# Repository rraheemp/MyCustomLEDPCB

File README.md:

# LED Driver Prototype System
## Overview
This project consist of a FPGA based board (Artix 7 Basys3) and a custom STM32-driven board with 2 IS31FL3743B SPI LED Matrix drivers and breakouts for adding other peripheral. Each LED can have its brightness and state controlled through the API functions. The FPGA will provide the master signals through a SPI header breakout on the custom board.

## Ideas for the future include:

- Desktop Dashboard GUI 
- IoT Dashboard

This is a personal project and as such, may not work 100% but is a continued learning experience for me. Feel free to use the code in your project if it seems useful or insightful.

### Renders:
#### Front: 

*This board has not be verified as of 3/21/2022 and should not be ordered until I verify it.*

## IS31Fl3743B

> The IS31FL3743B is a general purpose 18×n (n=1~11) 
LED Matrix programmed via 12MHz SPI interface. 
Each LED can be dimmed individually with 8-bit PWM 
data and 8-bit DC scaling data which allowing 256 
steps of linear PWM dimming and 256 steps of DC 
current adjustable level. -*Lumissil* 

### Library

The folder *IS31FL3743B Driver* contains the library of functions for illuminating the board. These functions are derived from the data sheet following the following SPI Data Scheme.

### Registers
There following tables define the registers and their appropriate values.
#### Pwm:

#### Scaling:

#### Configurations:

## *Coming Soon*

# STM32G031F6P6
> The STM32G031x4/x6/x8 mainstream microcontrollers are based on high-performance 
Arm® Cortex®-M0+ 32-bit RISC core operating at up to 64 MHz frequency. Offering a high 
level of integration, they are suitable for a wide range of applications in consumer, industrial 
and appliance domains and ready for the Internet of Things (IoT) solutions.

*ST*

## *Coming Soon*

# Basys 3 Artix-7 

> Complete and ready-to use digital circuit development platform, it includes enough switches, LEDs, and other I/O devices to allow a large number of designs to be completed without the need for any additional hardware. There are also enough uncommitted FPGA I/O pins to allow designs to be expanded using Digilent Pmods or other custom boards and circuits.

*Diligent*

## *Coming Soon*

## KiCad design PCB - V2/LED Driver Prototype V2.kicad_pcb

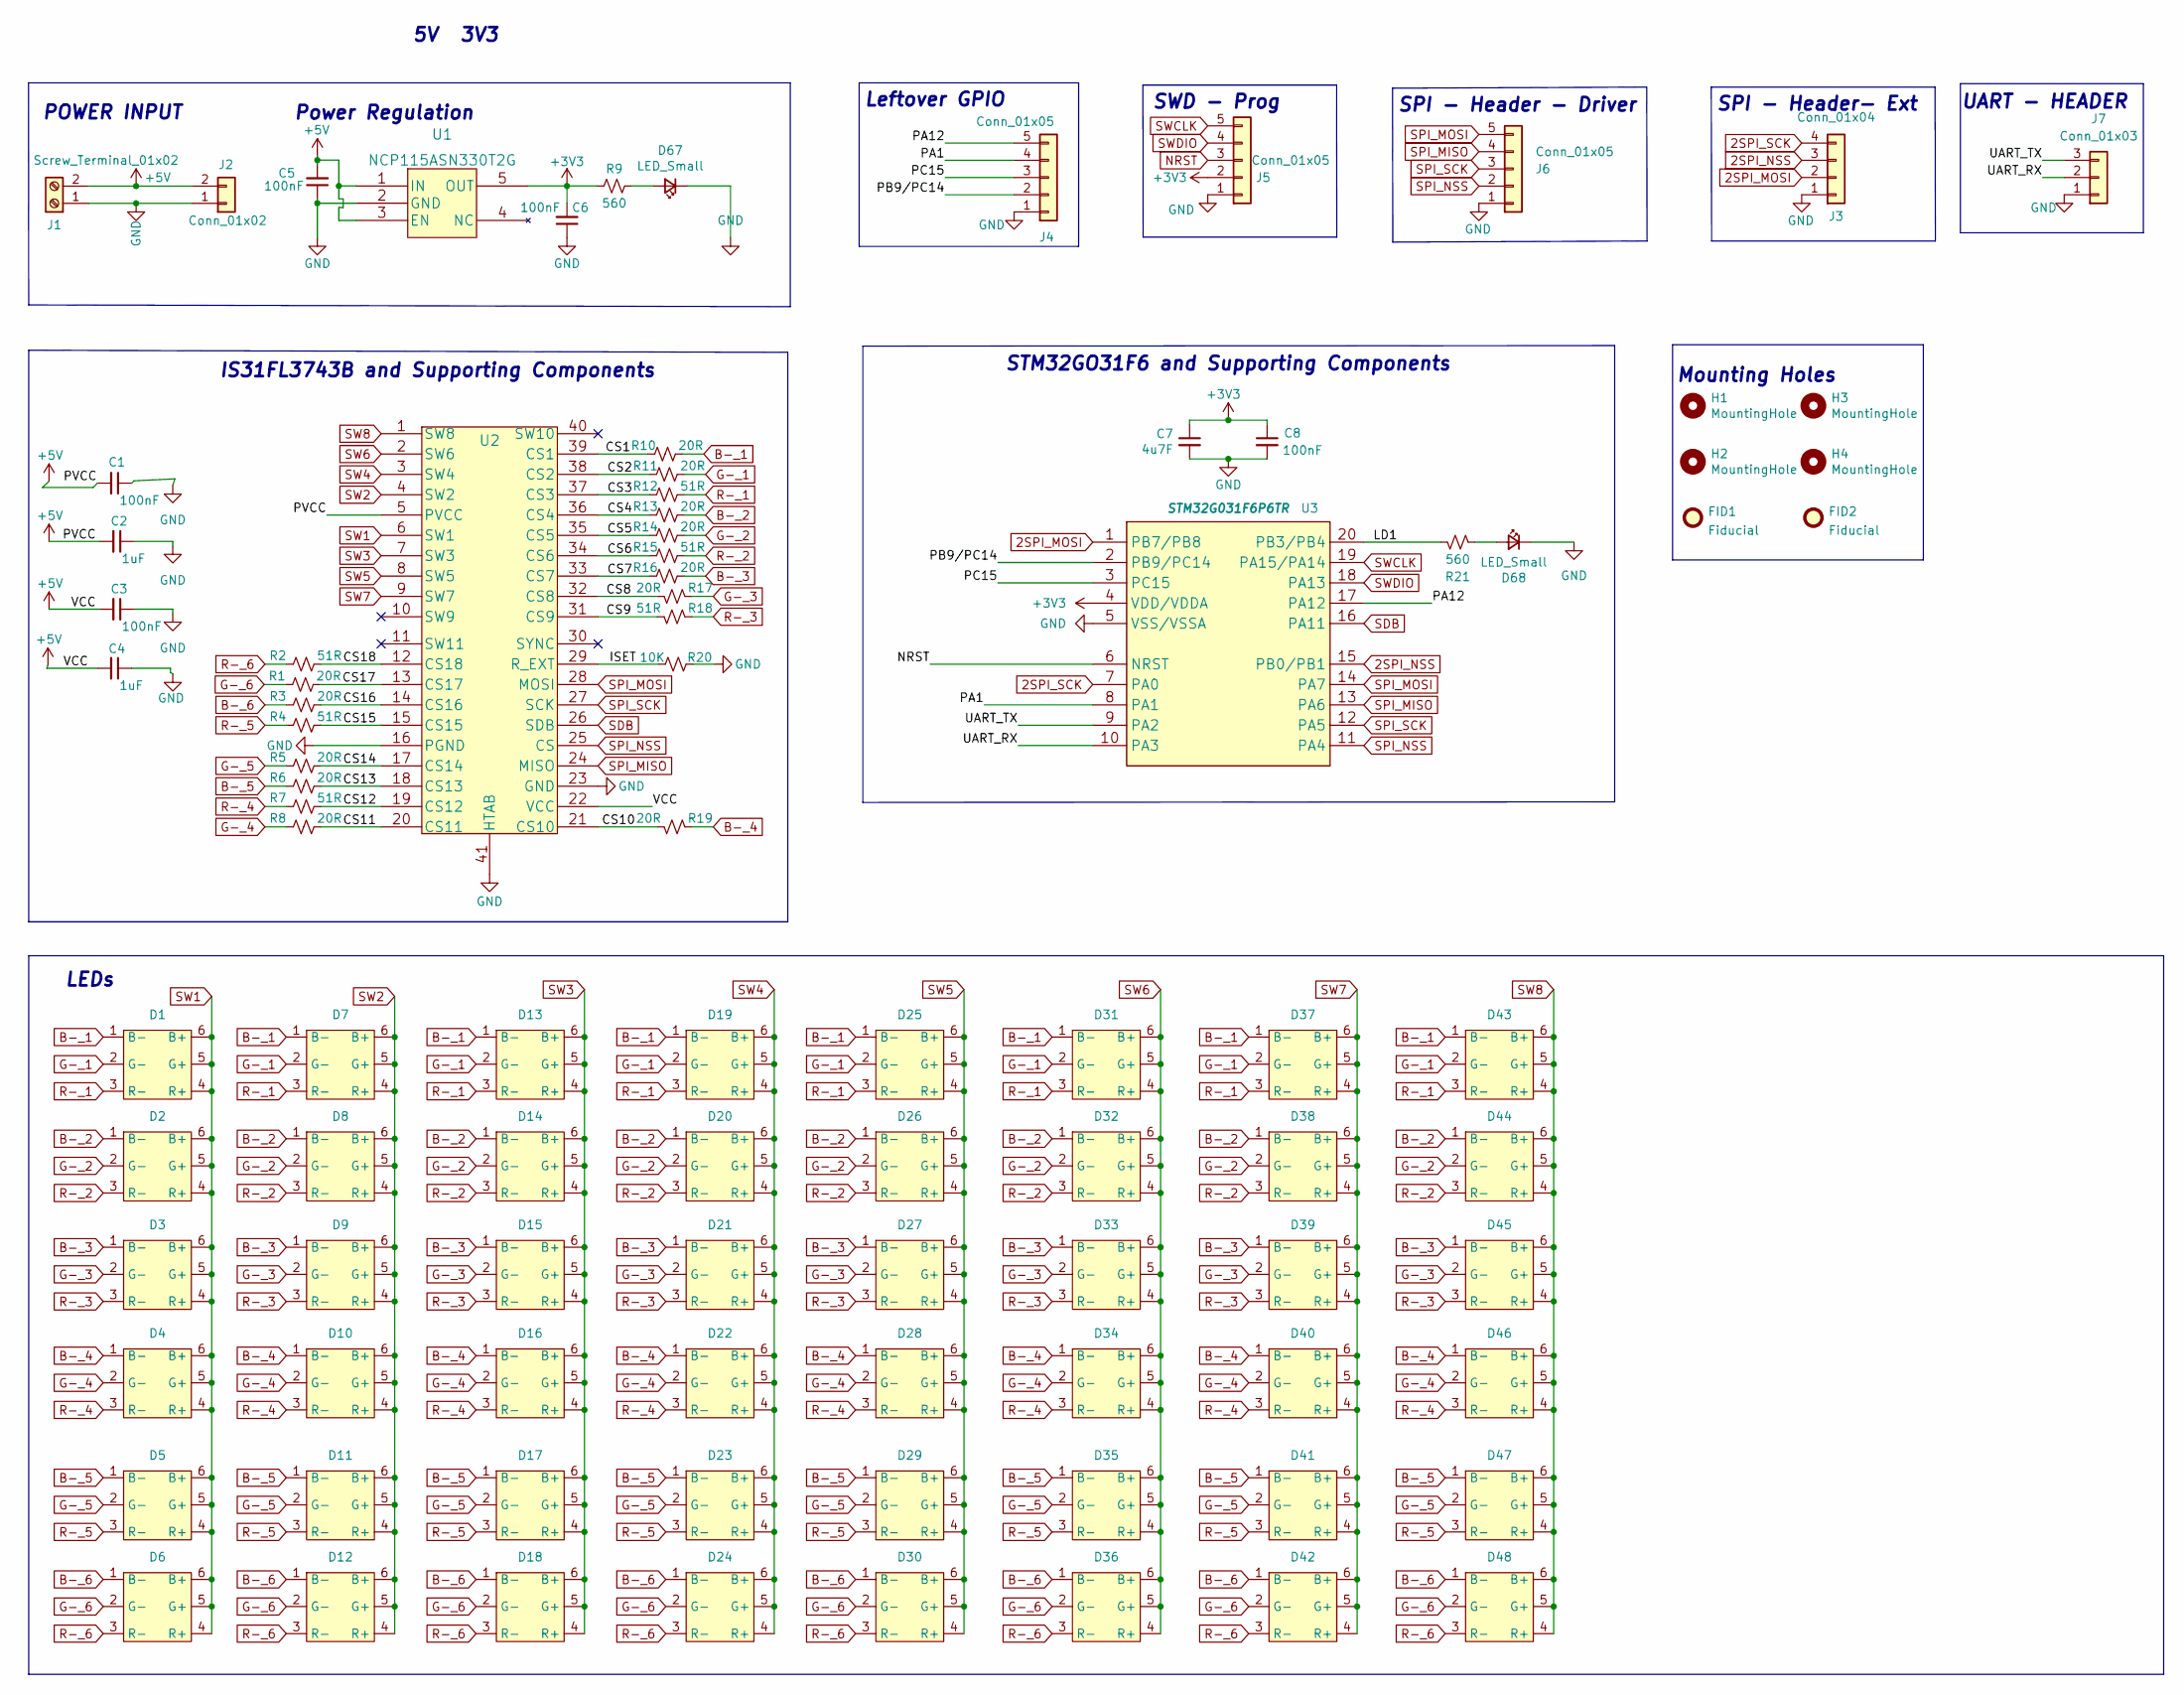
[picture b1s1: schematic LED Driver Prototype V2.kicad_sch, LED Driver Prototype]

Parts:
C1, C3, C5, C6, C8: 100nF; C_0603_1608Metric_Pad1.08x0.95mm_HandSolder
C2, C4: 1uF; C_0603_1608Metric_Pad1.08x0.95mm_HandSolder
C7: 4u7F; C_0603_1608Metric_Pad1.08x0.95mm_HandSolder
D1, D2, D3, D4, D5, D6, D7, D8, D9, D10, D11, D12, D13, D14, D15, D16, D17, D18, D19, D20, D21, D22, D23, D24, D25, D26, D27, D28, D29, D30, D31, D32, D33, D34, D35, D36, D37, D38, D39, D40, D41, D42, D43, D44, D45, D46, D47, D48: MHP3535RGBDT-S_-_PLCC_-_6; MHP3535RGBDT-S
D67: LED_Small; LTST-C191KRKT
D68: LED_Small; LTST-C191KGKT
FID1, FID2: Fiducial; Fiducial_0.5mm_Mask1.5mm
H1, H2, H3, H4: MountingHole; MountingHole_2.2mm_M2_ISO7380_Pad
J1: Screw_Terminal_01x02; TerminalBlock_TE_282834-2_1x02_P2.54mm_Horizontal
J2: Conn_01x02; PinHeader_1x02_P2.54mm_Vertical
J3: Conn_01x04; PinHeader_1x04_P2.54mm_Vertical
J4, J5, J6: Conn_01x05; PinHeader_1x05_P2.54mm_Vertical
J7: Conn_01x03; PinHeader_1x03_P2.54mm_Vertical
R1, R3, R5, R6, R8, R10, R11, R13, R14, R16, R17, R19: 20R; R_0603_1608Metric_Pad0.98x0.95mm_HandSolder
R2, R4, R7, R12, R15, R18: 51R; R_0603_1608Metric_Pad0.98x0.95mm_HandSolder
R9, R21: 560; R_0603_1608Metric_Pad0.98x0.95mm_HandSolder
R20: 10K; R_0603_1608Metric_Pad0.98x0.95mm_HandSolder
U1: NCP115ASN330T2G
U2: IS31FL3743B-QULS4-TR
U3: STM32G031F6P6TR; STM32G031F6P6

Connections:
2SPI_MOSI: J3.2, U3.1 (PB7/PB8)
2SPI_NSS: J3.3, U3.15 (PB0/PB1)
2SPI_SCK: J3.4, U3.7 (PA0)
+3V3: C6.2, C7.1, C8.1, J5.2, R9.2, U1.5 (OUT), U3.4 (VDD/VDDA)
+5V: C1.2, C2.2, C3.2, C4.2, C5.2, J1.2, J2.2, U1.1 (IN), U1.3 (EN), U2.5 (PVCC), U2.22 (VCC)
/CS1: R10.2, U2.39 (CS1)
/CS2: R11.2, U2.38 (CS2)
/CS3: R12.2, U2.37 (CS3)
/CS4: R13.2, U2.36 (CS4)
/CS5: R14.2, U2.35 (CS5)
/CS6: R15.2, U2.34 (CS6)
/CS7: R16.2, U2.33 (CS7)
/CS8: R17.1, U2.32 (CS8)
/CS9: R18.1, U2.31 (CS9)
/CS10: R19.1, U2.21 (CS10)
/CS11: R8.1, U2.20 (CS11)
/CS12: R7.1, U2.19 (CS12)
/CS13: R6.1, U2.18 (CS13)
/CS14: R5.1, U2.17 (CS14)
/CS15: R4.1, U2.15 (CS15)
/CS16: R3.1, U2.14 (CS16)
/CS17: R1.1, U2.13 (CS17)
/CS18: R2.1, U2.12 (CS18)
/ISET: R20.1, U2.29 (R_EXT)
/LD1: R21.2, U3.20 (PB3/PB4)
/PA1: J4.4, U3.8 (PA1)
/PA12: J4.5, U3.17 (PA12)
/PB9/PC14: J4.2, U3.2 (PB9/PC14)
/PC15: J4.3, U3.3 (PC15)
/UART_RX: J7.2, U3.10 (PA3)
/UART_TX: J7.3, U3.9 (PA2)
B-_1: D1.1 (B-), D7.1 (B-), D13.1 (B-), D19.1 (B-), D25.1 (B-), D31.1 (B-), D37.1 (B-), D43.1 (B-), R10.1
B-_2: D2.1 (B-), D8.1 (B-), D14.1 (B-), D20.1 (B-), D26.1 (B-), D32.1 (B-), D38.1 (B-), D44.1 (B-), R13.1
B-_3: D3.1 (B-), D9.1 (B-), D15.1 (B-), D21.1 (B-), D27.1 (B-), D33.1 (B-), D39.1 (B-), D45.1 (B-), R16.1
B-_4: D4.1 (B-), D10.1 (B-), D16.1 (B-), D22.1 (B-), D28.1 (B-), D34.1 (B-), D40.1 (B-), D46.1 (B-), R19.2
B-_5: D5.1 (B-), D11.1 (B-), D17.1 (B-), D23.1 (B-), D29.1 (B-), D35.1 (B-), D41.1 (B-), D47.1 (B-), R6.2
B-_6: D6.1 (B-), D12.1 (B-), D18.1 (B-), D24.1 (B-), D30.1 (B-), D36.1 (B-), D42.1 (B-), D48.1 (B-), R3.2
G-_1: D1.2 (G-), D7.2 (G-), D13.2 (G-), D19.2 (G-), D25.2 (G-), D31.2 (G-), D37.2 (G-), D43.2 (G-), R11.1
G-_2: D2.2 (G-), D8.2 (G-), D14.2 (G-), D20.2 (G-), D26.2 (G-), D32.2 (G-), D38.2 (G-), D44.2 (G-), R14.1
G-_3: D3.2 (G-), D9.2 (G-), D15.2 (G-), D21.2 (G-), D27.2 (G-), D33.2 (G-), D39.2 (G-), D45.2 (G-), R17.2
G-_4: D4.2 (G-), D10.2 (G-), D16.2 (G-), D22.2 (G-), D28.2 (G-), D34.2 (G-), D40.2 (G-), D46.2 (G-), R8.2
G-_5: D5.2 (G-), D11.2 (G-), D17.2 (G-), D23.2 (G-), D29.2 (G-), D35.2 (G-), D41.2 (G-), D47.2 (G-), R5.2
G-_6: D6.2 (G-), D12.2 (G-), D18.2 (G-), D24.2 (G-), D30.2 (G-), D36.2 (G-), D42.2 (G-), D48.2 (G-), R1.2
GND: C1.1, C2.1, C3.1, C4.1, C5.1, C6.1, C7.2, C8.2, D67.1 (K), D68.1 (K), J1.1, J2.1, J3.1, J4.1, J5.1, J6.1, J7.1, R20.2, U1.2 (GND), U2.16 (PGND), U2.23 (GND), U2.41 (HTAB), U3.5 (VSS/VSSA)
NRST: J5.3, U3.6 (NRST)
unnamed: D67.2 (A), R9.1
unnamed: D68.2 (A), R21.1
R-_1: D1.3 (R-), D7.3 (R-), D13.3 (R-), D19.3 (R-), D25.3 (R-), D31.3 (R-), D37.3 (R-), D43.3 (R-), R12.1
R-_2: D2.3 (R-), D8.3 (R-), D14.3 (R-), D20.3 (R-), D26.3 (R-), D32.3 (R-), D38.3 (R-), D44.3 (R-), R15.1
R-_3: D3.3 (R-), D9.3 (R-), D15.3 (R-), D21.3 (R-), D27.3 (R-), D33.3 (R-), D39.3 (R-), D45.3 (R-), R18.2
R-_4: D4.3 (R-), D10.3 (R-), D16.3 (R-), D22.3 (R-), D28.3 (R-), D34.3 (R-), D40.3 (R-), D46.3 (R-), R7.2
R-_5: D5.3 (R-), D11.3 (R-), D17.3 (R-), D23.3 (R-), D29.3 (R-), D35.3 (R-), D41.3 (R-), D47.3 (R-), R4.2
R-_6: D6.3 (R-), D12.3 (R-), D18.3 (R-), D24.3 (R-), D30.3 (R-), D36.3 (R-), D42.3 (R-), D48.3 (R-), R2.2
SDB: U2.26 (SDB), U3.16 (PA11)
SPI_MISO: J6.4, U2.24 (MISO), U3.13 (PA6)
SPI_MOSI: J6.5, U2.28 (MOSI), U3.14 (PA7)
SPI_NSS: J6.2, U2.25 (CS), U3.11 (PA4)
SPI_SCK: J6.3, U2.27 (SCK), U3.12 (PA5)
SW1: D1.4 (R+), D1.5 (G+), D1.6 (B+), D2.4 (R+), D2.5 (G+), D2.6 (B+), D3.4 (R+), D3.5 (G+), D3.6 (B+), D4.4 (R+), D4.5 (G+), D4.6 (B+), D5.4 (R+), D5.5 (G+), D5.6 (B+), D6.4 (R+), D6.5 (G+), D6.6 (B+), U2.6 (SW1)
SW2: D7.4 (R+), D7.5 (G+), D7.6 (B+), D8.4 (R+), D8.5 (G+), D8.6 (B+), D9.4 (R+), D9.5 (G+), D9.6 (B+), D10.4 (R+), D10.5 (G+), D10.6 (B+), D11.4 (R+), D11.5 (G+), D11.6 (B+), D12.4 (R+), D12.5 (G+), D12.6 (B+), U2.4 (SW2)
SW3: D13.4 (R+), D13.5 (G+), D13.6 (B+), D14.4 (R+), D14.5 (G+), D14.6 (B+), D15.4 (R+), D15.5 (G+), D15.6 (B+), D16.4 (R+), D16.5 (G+), D16.6 (B+), D17.4 (R+), D17.5 (G+), D17.6 (B+), D18.4 (R+), D18.5 (G+), D18.6 (B+), U2.7 (SW3)
SW4: D19.4 (R+), D19.5 (G+), D19.6 (B+), D20.4 (R+), D20.5 (G+), D20.6 (B+), D21.4 (R+), D21.5 (G+), D21.6 (B+), D22.4 (R+), D22.5 (G+), D22.6 (B+), D23.4 (R+), D23.5 (G+), D23.6 (B+), D24.4 (R+), D24.5 (G+), D24.6 (B+), U2.3 (SW4)
SW5: D25.4 (R+), D25.5 (G+), D25.6 (B+), D26.4 (R+), D26.5 (G+), D26.6 (B+), D27.4 (R+), D27.5 (G+), D27.6 (B+), D28.4 (R+), D28.5 (G+), D28.6 (B+), D29.4 (R+), D29.5 (G+), D29.6 (B+), D30.4 (R+), D30.5 (G+), D30.6 (B+), U2.8 (SW5)
SW6: D31.4 (R+), D31.5 (G+), D31.6 (B+), D32.4 (R+), D32.5 (G+), D32.6 (B+), D33.4 (R+), D33.5 (G+), D33.6 (B+), D34.4 (R+), D34.5 (G+), D34.6 (B+), D35.4 (R+), D35.5 (G+), D35.6 (B+), D36.4 (R+), D36.5 (G+), D36.6 (B+), U2.2 (SW6)
SW7: D37.4 (R+), D37.5 (G+), D37.6 (B+), D38.4 (R+), D38.5 (G+), D38.6 (B+), D39.4 (R+), D39.5 (G+), D39.6 (B+), D40.4 (R+), D40.5 (G+), D40.6 (B+), D41.4 (R+), D41.5 (G+), D41.6 (B+), D42.4 (R+), D42.5 (G+), D42.6 (B+), U2.9 (SW7)
SW8: D43.4 (R+), D43.5 (G+), D43.6 (B+), D44.4 (R+), D44.5 (G+), D44.6 (B+), D45.4 (R+), D45.5 (G+), D45.6 (B+), D46.4 (R+), D46.5 (G+), D46.6 (B+), D47.4 (R+), D47.5 (G+), D47.6 (B+), D48.4 (R+), D48.5 (G+), D48.6 (B+), U2.1 (SW8)
SWCLK: J5.5, U3.19 (PA15/PA14)
SWDIO: J5.4, U3.18 (PA13)

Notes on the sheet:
LEDs
STM32GO31F6 and Supporting Components
Power Regulation
Mounting Holes
3V3
SPI - Header- Ext
IS31FL3743B and Supporting Components
Leftover GPIO
UART - HEADER
SPI - Header - Driver
POWER INPUT
SWD - Prog

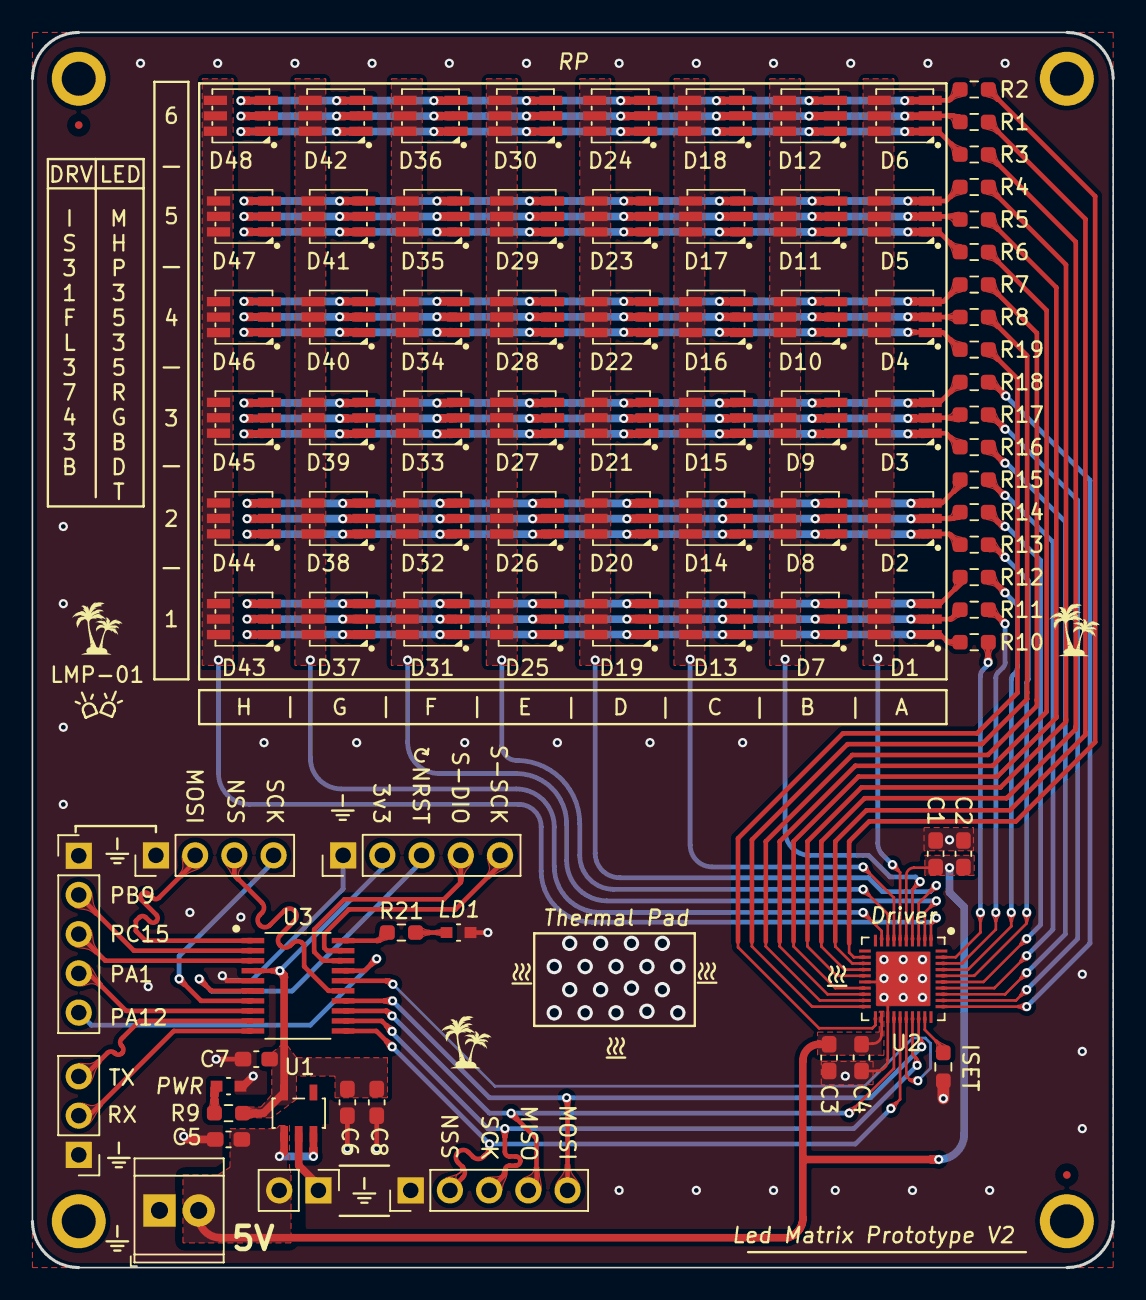
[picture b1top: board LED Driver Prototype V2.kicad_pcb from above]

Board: 2 copper layers, 70.0 x 80.0 mm, 95 parts (0 on the bottom side), 68 nets.

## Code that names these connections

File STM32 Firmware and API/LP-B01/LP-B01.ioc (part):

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Mcu.Name=STM32G031F(4-6-8)Px
Mcu.Package=TSSOP20
Mcu.UserName=STM32G031F6Px
PA11\ [PA9].GPIOParameters=GPIO_Label
PA11\ [PA9].GPIO_Label=SDB
PA11\ [PA9].Signal=GPIO_Output
PA13.Mode=Serial_Wire
PA13.Signal=SYS_SWDIO
PA14-BOOT0.Mode=Serial_Wire
PA14-BOOT0.Signal=SYS_SWCLK
PA2.Mode=Asynchronous
PA2.Signal=USART2_TX
PA3.Mode=Asynchronous
PA3.Signal=USART2_RX
PA4.Mode=NSS_Signal_Hard_Output
PA4.Signal=SPI1_NSS
PA5.Mode=Full_Duplex_Master
PA5.Signal=SPI1_SCK
PA6.Mode=Full_Duplex_Master
PA6.Signal=SPI1_MISO
PA7.Mode=Full_Duplex_Master
PA7.Signal=SPI1_MOSI
PB3.GPIOParameters=GPIO_Label
PB3.GPIO_Label=LD1
PB3.Signal=GPIO_Output
PB8.Mode=I2C
PB8.Signal=I2C1_SCL
PB9.Mode=I2C
PB9.Signal=I2C1_SDA
RCC.HSE_VALUE=8000000
RCC.SYSCLKFreq_VALUE=16000000
board=custom

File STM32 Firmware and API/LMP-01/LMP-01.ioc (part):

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Mcu.Name=STM32G031F(4-6-8)Px
Mcu.Package=TSSOP20
Mcu.UserName=STM32G031F6Px
PA0.Mode=Full_Duplex_Slave
PA0.Signal=SPI2_SCK
PA11\ [PA9].GPIOParameters=PinState,GPIO_Label
PA11\ [PA9].GPIO_Label=SDB
PA11\ [PA9].PinState=GPIO_PIN_RESET
PA11\ [PA9].Signal=GPIO_Output
PA13.Mode=Serial_Wire
PA13.Signal=SYS_SWDIO
PA14-BOOT0.Mode=Serial_Wire
PA14-BOOT0.Signal=SYS_SWCLK
PA2.Mode=Asynchronous
PA2.Signal=USART2_TX
PA3.Mode=Asynchronous
PA3.Signal=USART2_RX
PA4.GPIOParameters=PinState,GPIO_Label
PA4.GPIO_Label=CS
PA4.PinState=GPIO_PIN_SET
PA4.Signal=GPIO_Output
PA5.GPIOParameters=GPIO_Label
PA5.GPIO_Label=SCK
PA5.Mode=Full_Duplex_Master
PA5.Signal=SPI1_SCK
PA6.Mode=Full_Duplex_Master
PA6.Signal=SPI1_MISO
PA7.Mode=Full_Duplex_Master
PA7.Signal=SPI1_MOSI
PB2.Mode=Full_Duplex_Slave
PB2.Signal=SPI2_MISO
PB4.GPIOParameters=GPIO_Speed,PinState,GPIO_Label,GPIO_ModeDefaultOutputPP
PB4.GPIO_Label=LD1
PB4.GPIO_ModeDefaultOutputPP=GPIO_MODE_OUTPUT_PP
PB4.GPIO_Speed=GPIO_SPEED_FREQ_MEDIUM
PB4.PinState=GPIO_PIN_RESET
PB4.Signal=GPIO_Output
PB7.Mode=Full_Duplex_Slave
PB7.Signal=SPI2_MOSI
RCC.HSE_VALUE=8000000
RCC.SYSCLKFreq_VALUE=64000000
RCC.SYSCLKSource=RCC_SYSCLKSOURCE_PLLCLK
board=custom

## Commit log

2022-03-24 Major code work
2022-03-25 Numbers fixed
2022-03-27 Minor Changes

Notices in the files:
parts and their libraries:
Copyright 2021 Accelerated Designs. All rights reserved.
